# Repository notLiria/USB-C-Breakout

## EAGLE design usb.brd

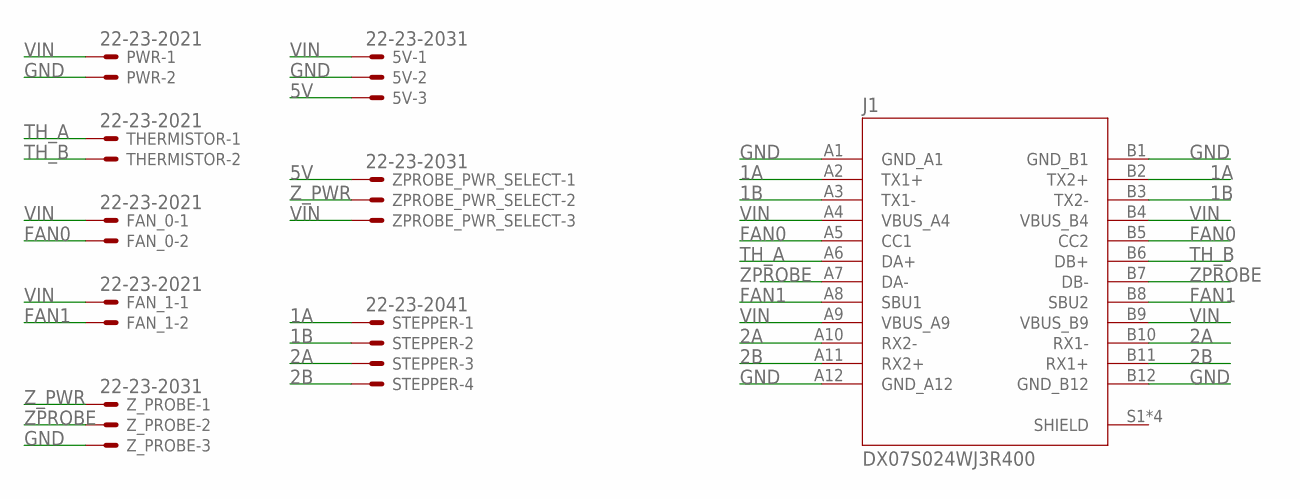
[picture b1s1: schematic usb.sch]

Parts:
5V: 22-23-2031
FAN_0, FAN_1: 22-23-2021
J1: DX07S024WJ3R400; JAE_DX07S024WJ3R400
PWR: 22-23-2021
STEPPER: 22-23-2041
THERMISTOR: 22-23-2021
ZPROBE_PWR_SELECT: 22-23-2031
Z_PROBE: 22-23-2031

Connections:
1A: J1.A2 (TX1+), J1.B2 (TX2+), STEPPER.1
1B: J1.A3 (TX1-), J1.B3 (TX2-), STEPPER.2
2A: J1.A10 (RX2-), J1.B10 (RX1-), STEPPER.3
2B: J1.A11 (RX2+), J1.B11 (RX1+), STEPPER.4
5V: 5V.3, ZPROBE_PWR_SELECT.1
FAN0: FAN_0.2, J1.A5 (CC1), J1.B5 (CC2)
FAN1: FAN_1.2, J1.A8 (SBU1), J1.B8 (SBU2)
GND: 5V.2, J1.A1 (GND_A1), J1.A12 (GND_A12), J1.B1 (GND_B1), J1.B12 (GND_B12), PWR.2, Z_PROBE.3
TH_A: J1.A6 (DA+), THERMISTOR.1
TH_B: J1.B6 (DB+), THERMISTOR.2
VIN: 5V.1, FAN_0.1, FAN_1.1, J1.A4 (VBUS_A4), J1.A9 (VBUS_A9), J1.B4 (VBUS_B4), J1.B9 (VBUS_B9), PWR.1, ZPROBE_PWR_SELECT.3
ZPROBE: J1.A7 (DA-), J1.B7 (DB-), Z_PROBE.2
Z_PWR: ZPROBE_PWR_SELECT.2, Z_PROBE.1

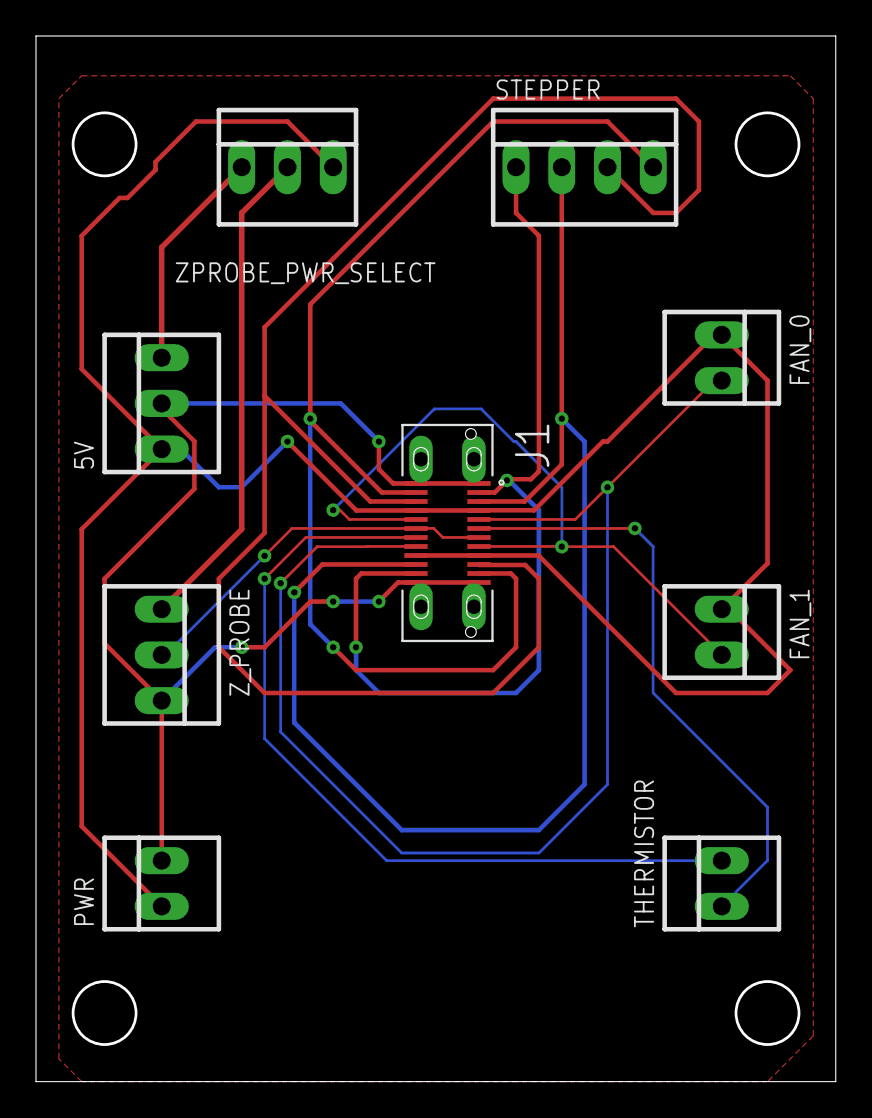
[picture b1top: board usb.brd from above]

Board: 2 copper layers, 44.3 x 57.9 mm, 9 parts (0 on the bottom side), 13 nets.

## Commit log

2020-07-24 Changed to vertical plug
